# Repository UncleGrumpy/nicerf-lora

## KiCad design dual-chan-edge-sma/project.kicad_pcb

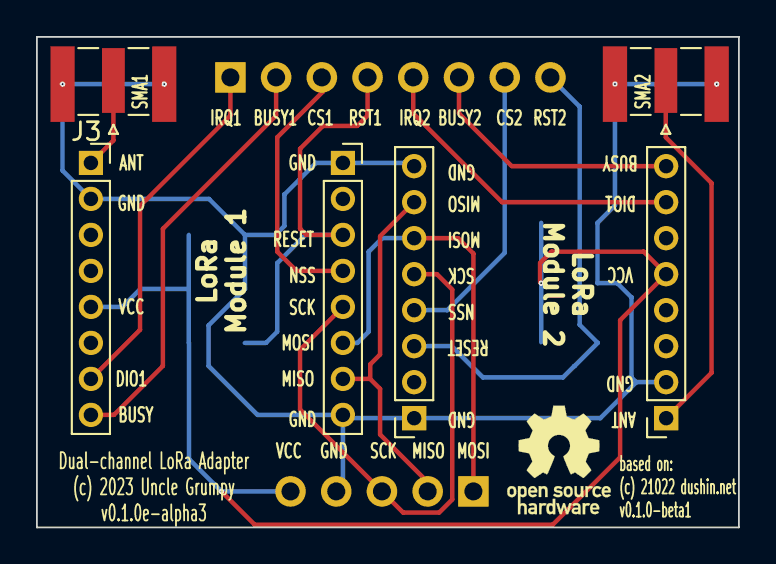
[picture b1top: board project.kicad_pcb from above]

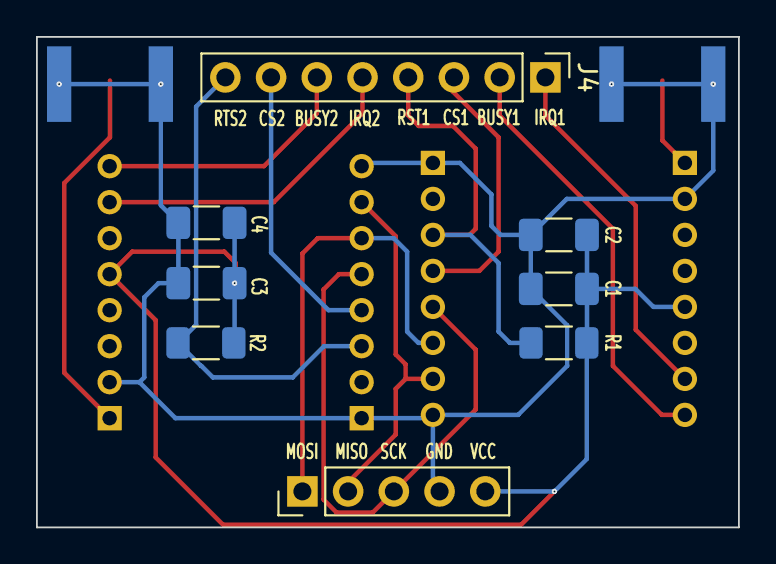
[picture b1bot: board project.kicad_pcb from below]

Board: 2 copper layers, 39.0 x 27.2 mm, 14 parts (8 on the bottom side), 15 nets.

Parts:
C1, C3: 100nF; C_1206_3216Metric_Pad1.33x1.80mm_HandSolder
C2, C4: 10uF; C_1206_3216Metric_Pad1.33x1.80mm_HandSolder
J1, J2, J5, J6: Conn_01x08_Female; PinSocket_1x08_P2.00mm_Vertical
J3: Conn_01x02_Female; SMA_Samtec_SMA-J-P-X-ST-EM1_EdgeMount
J4: Conn_01x04_Male; PinHeader_1x08_P2.54mm_Vertical
J9: Conn_01x05_Male; PinHeader_1x05_P2.54mm_Vertical
R1, R2: 10k; R_1206_3216Metric_Pad1.30x1.75mm_HandSolder
SMA2: SMA_Samtec_SMA-J-P-X-ST-EM1_EdgeMount

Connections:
/ANT1: J1.1, J3.1
/ANT2: J5.1, SMA2.1
/BUSY1: J1.8, J4.2
/BUSY2: J4.6, J5.8
/CS1: J2.4, J4.3
/CS2: J4.7, J6.4
/GND: C1.2, C2.2, C3.2, C4.2, J1.2, J2.1, J2.8, J3.1 (Pin_2), J3.2, J5.2, J6.1, J6.8, J9.4, SMA2.1, SMA2.2
/IRQ1: J1.7, J4.1
/IRQ2: J4.5, J5.7
/MISO: J2.7, J6.7, J9.2
/MOSI: J2.6, J6.6, J9.1
/RESET1: J2.3, J4.4, R1.1
/RESET2: J4.8, J6.3, R2.1
/SCK: J2.5, J6.5, J9.3
/VCC: C1.1, C2.1, C3.1, C4.1, J1.5, J5.5, J9.5, R1.2, R2.2

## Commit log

2023-07-20 Add edge-mount sma dual board variation: v0.1.0e-alpha1
    First layout of edge-mount SMA antenna connector replacing u.fl connector.
2023-07-20 Version 0.1.0e-alpha3
    Moves the SMA connectords to opposite sides of the board and flips LoRa module 2
    180 degrees. Silkscreen lettering flipped on module 2 to give better visual
    indication of orientation.

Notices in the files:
dual-chan-edge-sma/project.kicad_pcb:
(c) 2023 Uncle Grumpy
